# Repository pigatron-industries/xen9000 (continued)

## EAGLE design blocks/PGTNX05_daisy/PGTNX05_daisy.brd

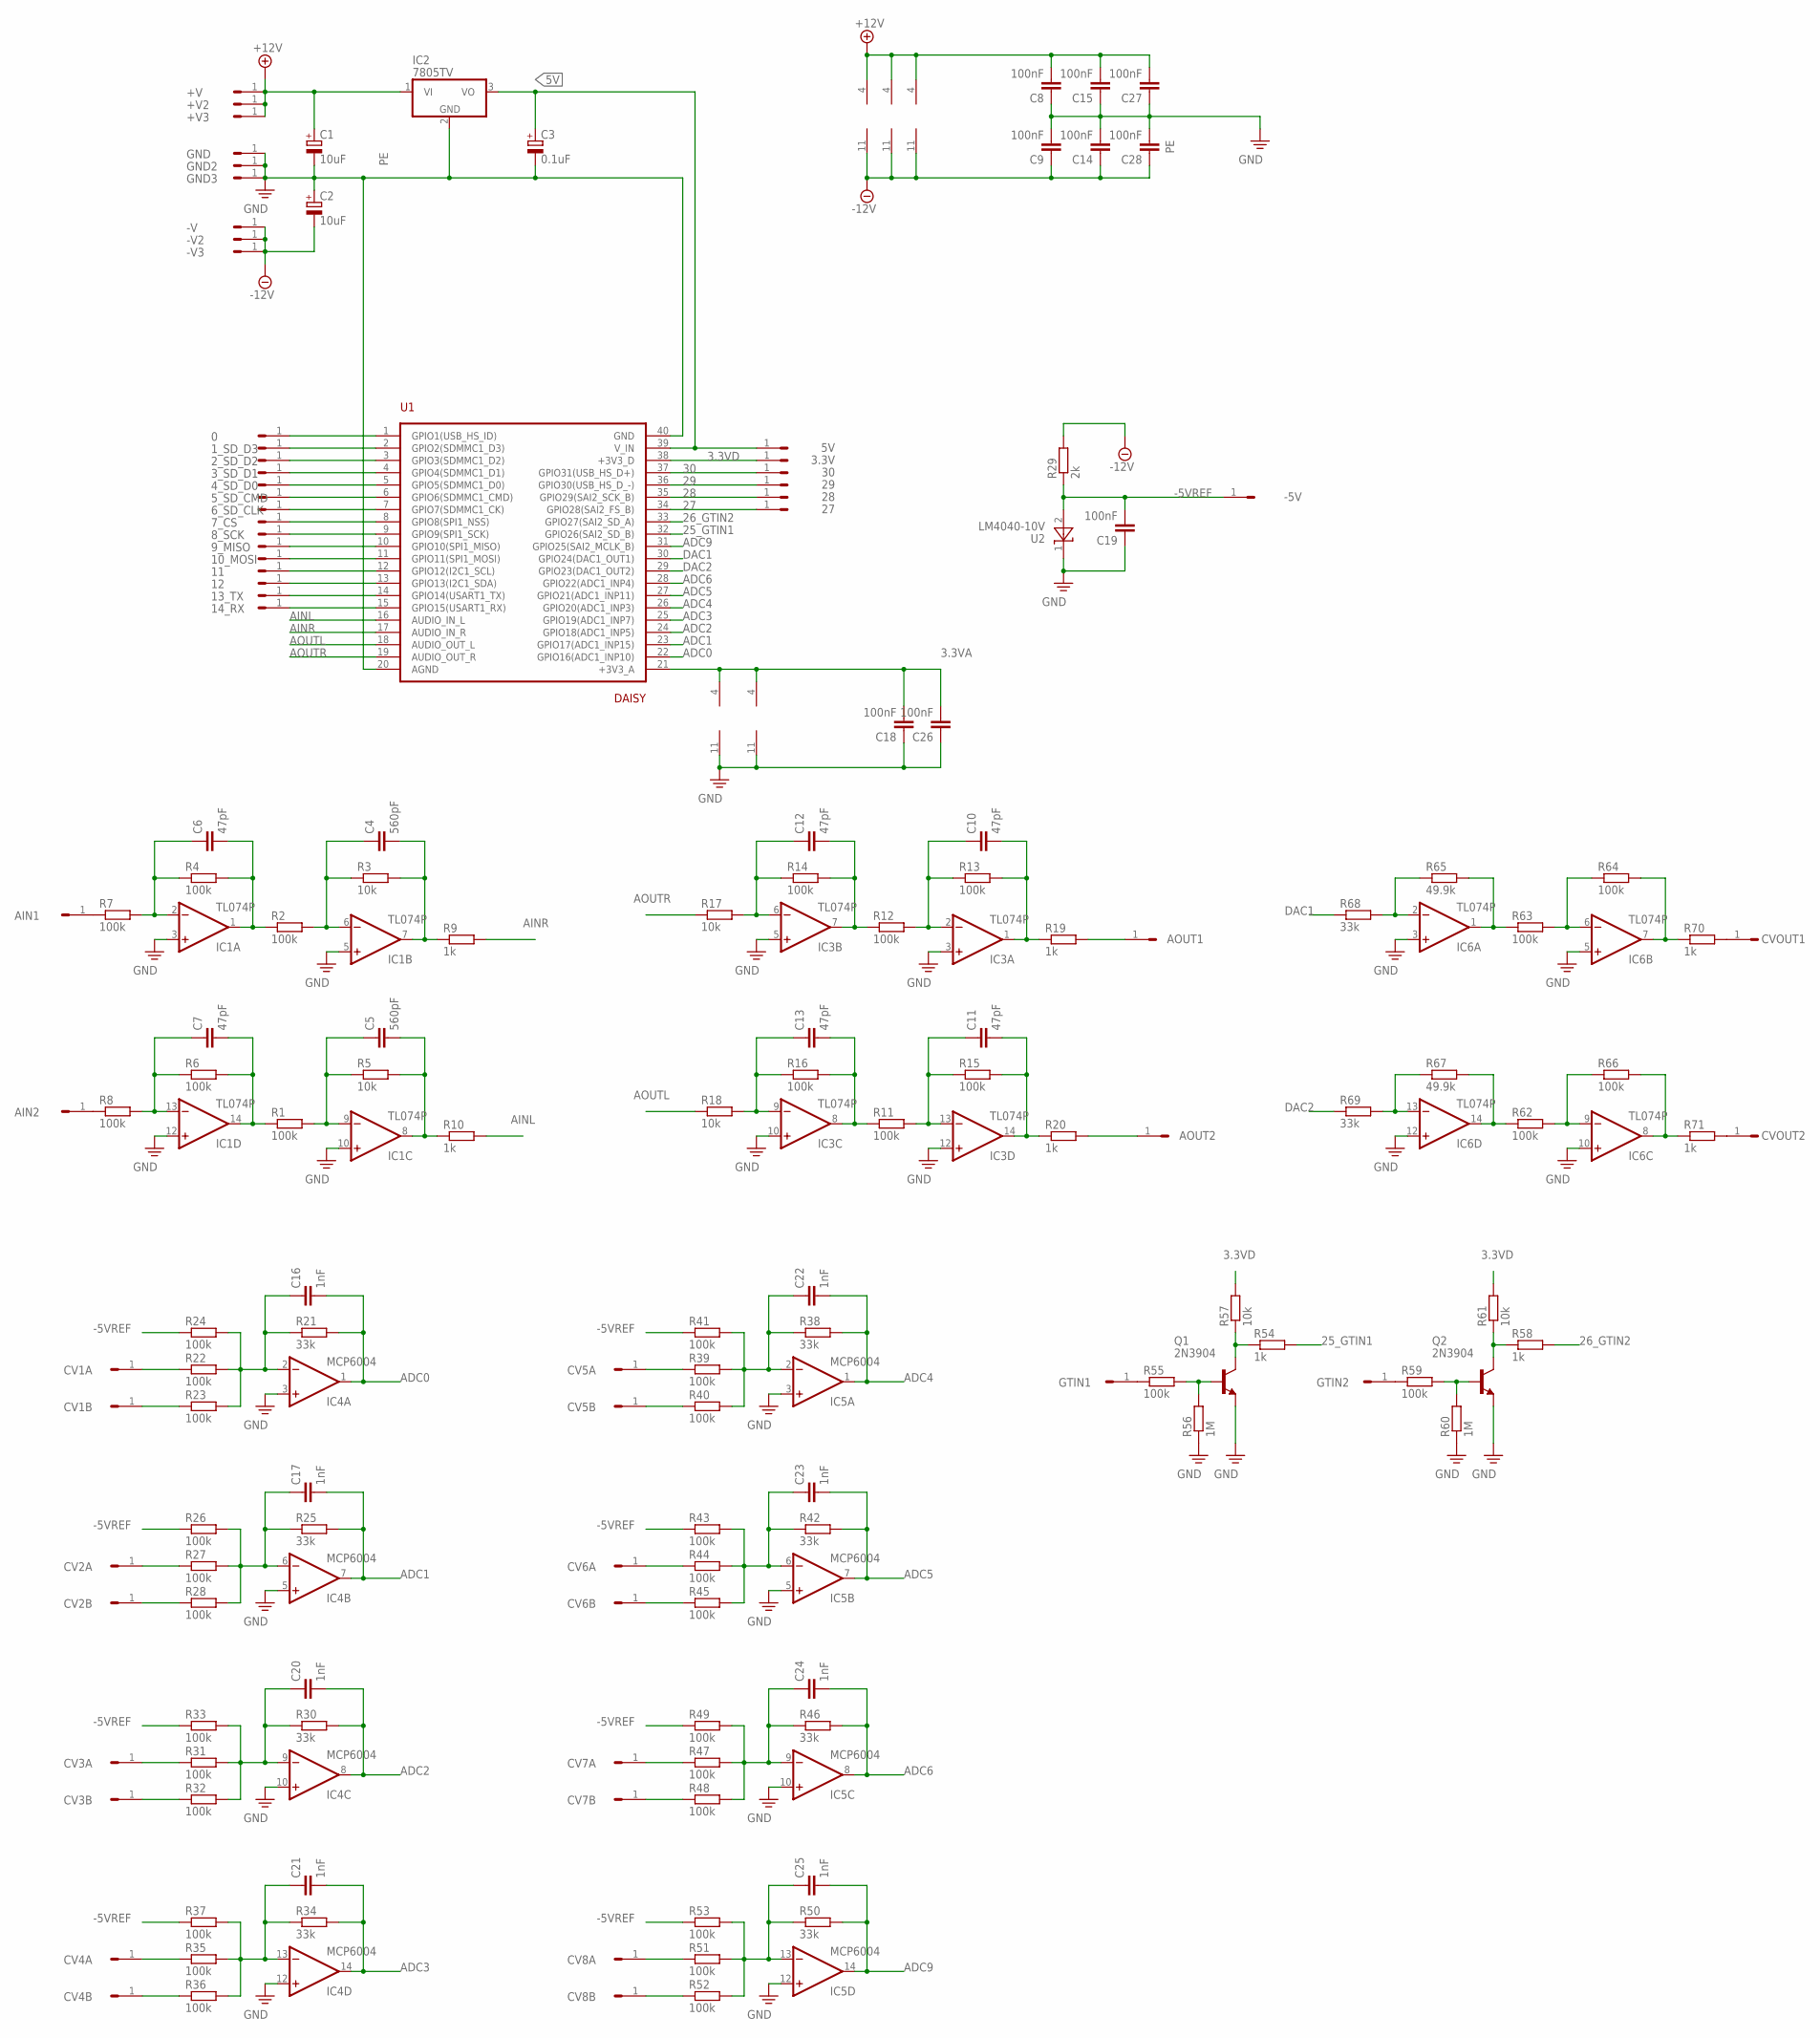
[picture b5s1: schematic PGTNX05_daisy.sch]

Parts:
0, 1_SD_D3, 2_SD_D2, 3.3V, 3_SD_D1, 4_SD_D0, 5V, 5_SD_CMD, 6_SD_CLK, 7_CS, 8_SCK, 9_MISO, 10_MOSI, 11, 12, 13_TX, 14_RX, 27, 28, 29, 30: HEADER/MALE/01
+V, +V2, +V3: HEADER/MALE/01
-5V: HEADER/MALE/01
-V, -V2, -V3: HEADER/MALE/01
AIN1, AIN2: HEADER/MALE/01
AOUT1, AOUT2: HEADER/MALE/01
C1, C2: 10uF; E2,5-6
C3: 0.1uF; E2,5-6
C4, C5: 560pF; CERAMICDISC/5
C6, C7, C10, C11, C12, C13: 47pF; CERAMICDISC/5
C8, C9, C14, C15, C18, C19, C26, C27, C28: 100nF; CERAMICDISC/5
C16, C17, C20, C21, C22, C23, C24, C25: 1nF; CERAMICDISC/5
CV1A, CV1B, CV2A, CV2B, CV3A, CV3B, CV4A, CV4B, CV5A, CV5B, CV6A, CV6B, CV7A, CV7B, CV8A, CV8B: HEADER/MALE/01
CVOUT1, CVOUT2: HEADER/MALE/01
GND, GND2, GND3: HEADER/MALE/01
GTIN1, GTIN2: HEADER/MALE/01
IC1, IC3, IC6: TL074P; DIL14
IC2: 7805TV; TO220V
IC4, IC5: MCP6004; DIL14
Q1, Q2: 2N3904; TO92
R1, R2, R4, R6, R7, R8, R11, R12, R13, R14, R15, R16, R22, R23, R24, R26, R27, R28, R31, R32, R33, R35, R36, R37, R39, R40, R41, R43, R44, R45, R47, R48, R49, R51, R52, R53, R55, R59, R62, R63, R64, R66: 100k; RESISTOR/7.5
R3, R5, R17, R18, R57, R61: 10k; RESISTOR/7.5
R9, R10, R19, R20, R54, R58, R70, R71: 1k; RESISTOR/7.5
R21, R25, R30, R34, R38, R42, R46, R50, R68, R69: 33k; RESISTOR/7.5
R29: 2k; RESISTOR/7.5
R56, R60: 1M; RESISTOR/7.5
R65, R67: 49.9k; RESISTOR/7.5
U1: DAISY; ES_DAISY_SEED
U2: LM4040-10V; SOT-23

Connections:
3.3VA: C18.2, C26.2, IC4.4 (V+), IC5.4 (V+), U1.21 (+3V3_A)
3.3VD: 3.3V.1, R57.2, R61.2, U1.38 (+3V3_D)
5V: 5V.1, C3.+, IC2.3 (VO), U1.39 (V_IN)
25_GTIN1: R54.2, U1.32 (GPIO26(SAI2_SD_B))
26_GTIN2: R58.2, U1.33 (GPIO27(SAI2_SD_A))
27: 27.1, U1.34 (GPIO28(SAI2_FS_B))
28: 28.1, U1.35 (GPIO29(SAI2_SCK_B))
29: 29.1, U1.36 (GPIO30(USB_HS_D_-))
30: 30.1, U1.37 (GPIO31(USB_HS_D+))
+12V: +V.1, +V2.1, +V3.1, C1.+, C8.2, C15.2, C27.2, IC1.4 (V+), IC2.1 (VI), IC3.4 (V+), IC6.4 (V+)
-5VREF: -5V.1, C19.2, R24.1, R26.1, R29.1, R33.1, R37.1, R41.1, R43.1, R49.1, R53.1, U2.2 (A)
-12V: -V.1, -V2.1, -V3.1, C2.-, C9.1, C14.1, C28.1, IC1.11 (V-), IC3.11 (V-), IC6.11 (V-), R29.2
ADC0: C16.2, IC4.1 (OUT), R21.2, U1.22 (GPIO16(ADC1_INP10))
ADC1: C17.2, IC4.7 (OUT), R25.2, U1.23 (GPIO17(ADC1_INP15))
ADC2: C20.2, IC4.8 (OUT), R30.2, U1.24 (GPIO18(ADC1_INP5))
ADC3: C21.2, IC4.14 (OUT), R34.2, U1.25 (GPIO19(ADC1_INP7))
ADC4: C22.2, IC5.1 (OUT), R38.2, U1.26 (GPIO20(ADC1_INP3))
ADC5: C23.2, IC5.7 (OUT), R42.2, U1.27 (GPIO21(ADC1_INP11))
ADC6: C24.2, IC5.8 (OUT), R46.2, U1.28 (GPIO22(ADC1_INP4))
ADC9: C25.2, IC5.14 (OUT), R50.2, U1.31 (GPIO25(SAI2_MCLK_B))
AINL: R10.2, U1.16 (AUDIO_IN_L)
AINR: R9.2, U1.17 (AUDIO_IN_R)
AOUTL: R18.1, U1.18 (AUDIO_OUT_L)
AOUTR: R17.1, U1.19 (AUDIO_OUT_R)
DAC1: R68.1, U1.30 (GPIO24(DAC1_OUT1))
DAC2: R69.1, U1.29 (GPIO23(DAC1_OUT2))
unnamed: CV2A.1, R27.1
unnamed: C7.2, IC1.14 (OUT), R1.1, R6.2
unnamed: C6.2, IC1.1 (OUT), R2.1, R4.2
unnamed: C4.1, IC1.6 (-IN), R2.2, R3.1
unnamed: C5.1, IC1.9 (-IN), R1.2, R5.1
unnamed: AIN1.1, R7.1
unnamed: AIN2.1, R8.1
unnamed: C7.1, IC1.13 (-IN), R6.1, R8.2
unnamed: C5.2, IC1.8 (OUT), R5.2, R10.1
unnamed: C4.2, IC1.7 (OUT), R3.2, R9.1
unnamed: AOUT1.1, R19.2
unnamed: C12.2, IC3.7 (OUT), R12.1, R14.2
unnamed: C6.1, IC1.2 (-IN), R4.1, R7.2
unnamed: C10.1, IC3.2 (-IN), R12.2, R13.1
unnamed: C13.2, IC3.8 (OUT), R11.1, R16.2
unnamed: C11.1, IC3.13 (-IN), R11.2, R15.1
unnamed: C13.1, IC3.9 (-IN), R16.1, R18.2
unnamed: C11.2, IC3.14 (OUT), R15.2, R20.1
unnamed: C10.2, IC3.1 (OUT), R13.2, R19.1
unnamed: C12.1, IC3.6 (-IN), R14.1, R17.2
unnamed: AOUT2.1, R20.2
unnamed: CV1A.1, R22.1
unnamed: 14_RX.1, U1.15 (GPIO15(USART1_RX))
unnamed: C16.1, IC4.2 (-IN), R21.1, R22.2, R23.2, R24.2
unnamed: GTIN2.1, R59.1
unnamed: CV2B.1, R28.1
unnamed: CV1B.1, R23.1
unnamed: 13_TX.1, U1.14 (GPIO14(USART1_TX))
unnamed: C17.1, IC4.6 (-IN), R25.1, R26.2, R27.2, R28.2
unnamed: C21.1, IC4.13 (-IN), R34.1, R35.2, R36.2, R37.2
unnamed: CV4A.1, R35.1
unnamed: CV4B.1, R36.1
unnamed: 10_MOSI.1, U1.11 (GPIO11(SPI1_MOSI))
unnamed: CV3B.1, R32.1
unnamed: CV3A.1, R31.1
unnamed: C20.1, IC4.9 (-IN), R30.1, R31.2, R32.2, R33.2
unnamed: 9_MISO.1, U1.10 (GPIO10(SPI1_MISO))
unnamed: C22.1, IC5.2 (-IN), R38.1, R39.2, R40.2, R41.2
unnamed: 8_SCK.1, U1.9 (GPIO9(SPI1_SCK))
unnamed: CV5B.1, R40.1
unnamed: CV5A.1, R39.1
unnamed: 7_CS.1, U1.8 (GPIO8(SPI1_NSS))
unnamed: C23.1, IC5.6 (-IN), R42.1, R43.2, R44.2, R45.2
unnamed: CV6A.1, R44.1
unnamed: CV6B.1, R45.1
unnamed: C25.1, IC5.13 (-IN), R50.1, R51.2, R52.2, R53.2
unnamed: 6_SD_CLK.1, U1.7 (GPIO7(SDMMC1_CK))
unnamed: CV8A.1, R51.1
unnamed: CV8B.1, R52.1
unnamed: CV7B.1, R48.1
unnamed: CV7A.1, R47.1
unnamed: C24.1, IC5.9 (-IN), R46.1, R47.2, R48.2, R49.2
unnamed: 5_SD_CMD.1, U1.6 (GPIO6(SDMMC1_CMD))
unnamed: GTIN1.1, R55.1
unnamed: Q1.2 (B), R55.2, R56.2
unnamed: Q1.1 (C), R54.1, R57.1
unnamed: Q2.2 (B), R59.2, R60.2
unnamed: Q2.1 (C), R58.1, R61.1
unnamed: 4_SD_D0.1, U1.5 (GPIO5(SDMMC1_D0))
unnamed: 3_SD_D1.1, U1.4 (GPIO4(SDMMC1_D1))
unnamed: 2_SD_D2.1, U1.3 (GPIO3(SDMMC1_D2))
unnamed: 1_SD_D3.1, U1.2 (GPIO2(SDMMC1_D3))
unnamed: 0.1, U1.1 (GPIO1(USB_HS_ID))
unnamed: 11.1, U1.12 (GPIO12(I2C1_SCL))
unnamed: 12.1, U1.13 (GPIO13(I2C1_SDA))
unnamed: IC6.1 (OUT), R63.1, R65.2
unnamed: IC6.6 (-IN), R63.2, R64.1
unnamed: IC6.14 (OUT), R62.1, R67.2
unnamed: IC6.9 (-IN), R62.2, R66.1
unnamed: IC6.13 (-IN), R67.1, R69.2
unnamed: IC6.8 (OUT), R66.2, R71.1
unnamed: IC6.7 (OUT), R64.2, R70.1
unnamed: IC6.2 (-IN), R65.1, R68.2
unnamed: CVOUT1.1, R70.2
unnamed: CVOUT2.1, R71.2
PE: C1.-, C2.+, C3.-, C8.1, C9.2, C14.2, C15.1, C18.1, C19.1, C26.1, C27.1, C28.2, GND.1, GND2.1, GND3.1, IC1.3 (+IN), IC1.5 (+IN), IC1.10 (+IN), IC1.12 (+IN), IC2.2 (GND), IC3.3 (+IN), IC3.5 (+IN), IC3.10 (+IN), IC3.12 (+IN), IC4.3 (+IN), IC4.5 (+IN), IC4.10 (+IN), IC4.11 (V-), IC4.12 (+IN), IC5.3 (+IN), IC5.5 (+IN), IC5.10 (+IN), IC5.11 (V-), IC5.12 (+IN), IC6.3 (+IN), IC6.5 (+IN), IC6.10 (+IN), IC6.12 (+IN), Q1.3 (E), Q2.3 (E), R56.1, R60.1, U1.20 (AGND), U1.40 (GND), U2.1 (C)

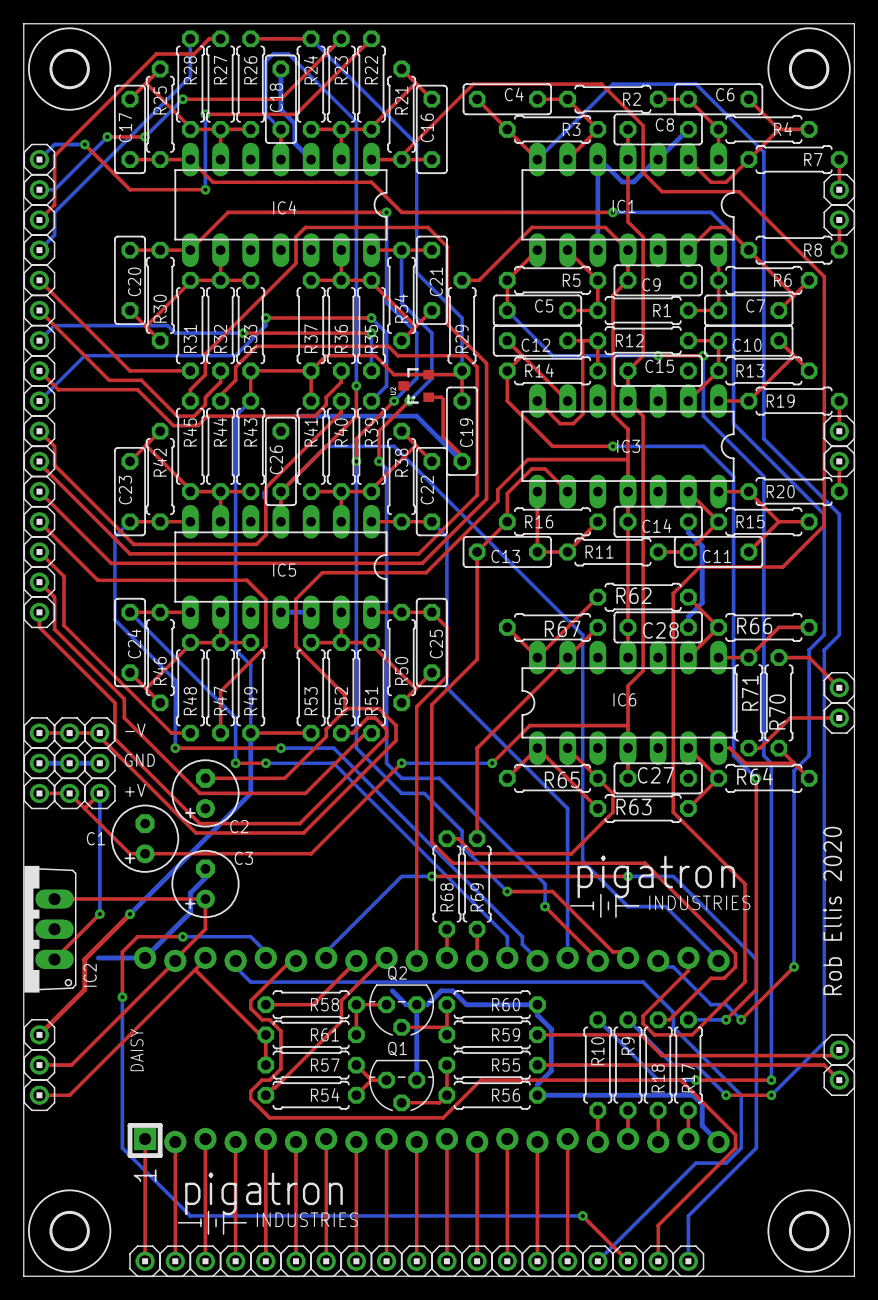
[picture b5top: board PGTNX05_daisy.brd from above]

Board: 2 copper layers, 69.9 x 105.4 mm, 170 parts (0 on the bottom side), 102 nets.

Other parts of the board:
U$1, U$5: PIGATRON-LOGO
U$2, U$3, U$4, U$7: STANDOFF/3.0

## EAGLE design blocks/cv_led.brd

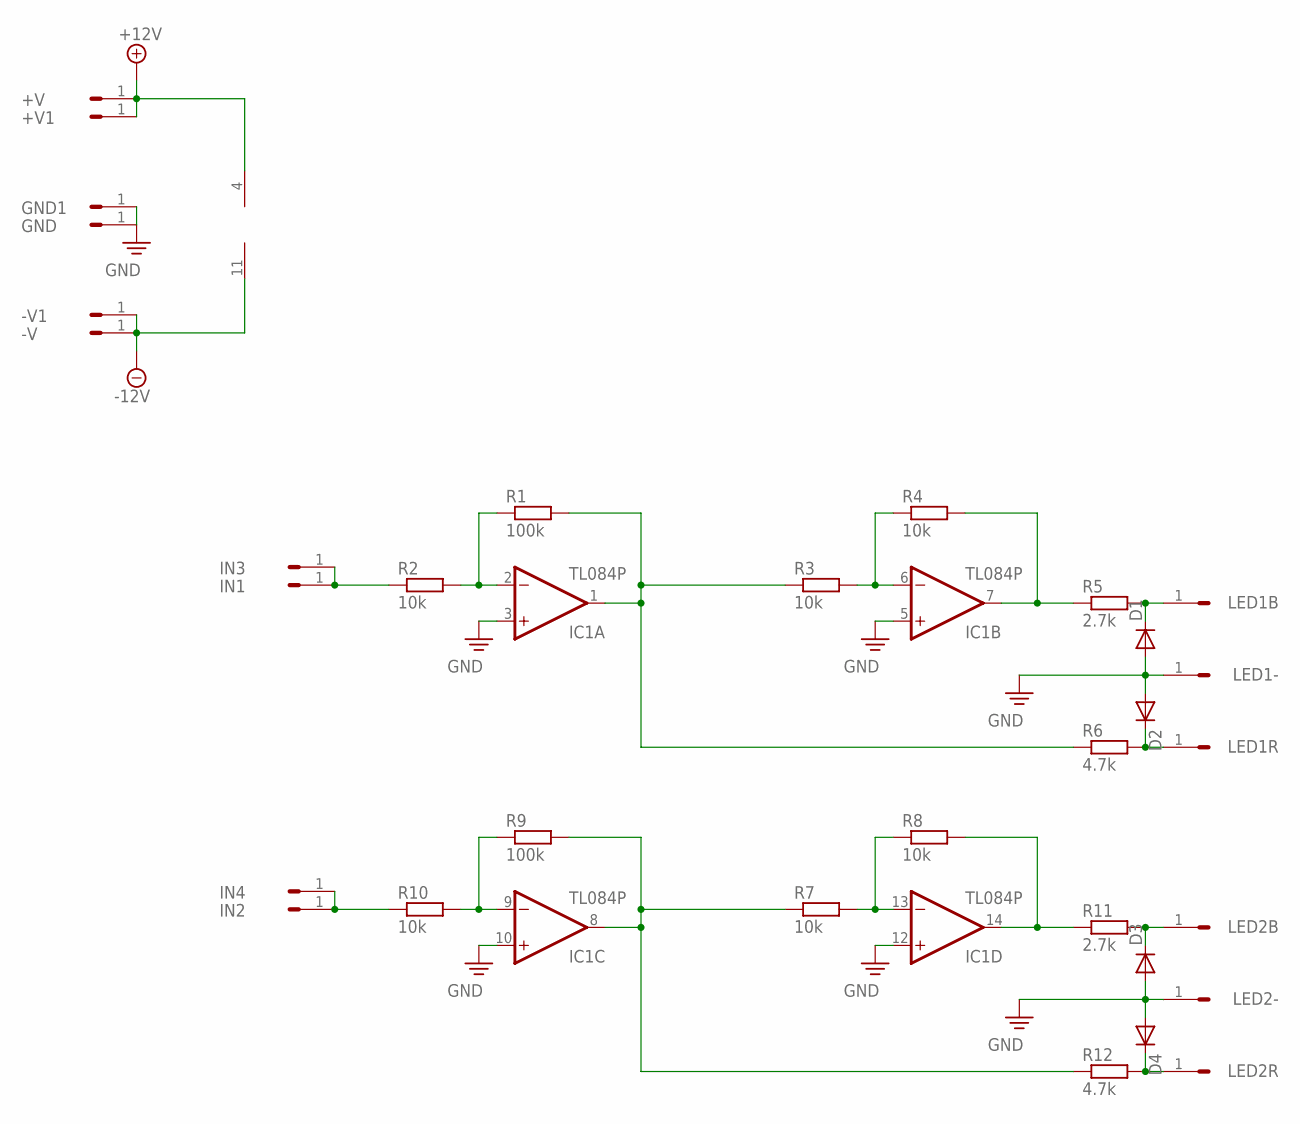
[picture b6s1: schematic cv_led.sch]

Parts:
+V, +V1: HEADER/MALE/01
-V, -V1: HEADER/MALE/01
D1, D2, D3, D4: 1N4148DO35-7; DO35-7
GND, GND1: HEADER/MALE/01
IC1: TL084P; DIL14
IN1, IN2, IN3, IN4: HEADER/MALE/01
LED1-, LED1B, LED1R, LED2-, LED2B, LED2R: HEADER/MALE/01
R1, R9: 100k; RESISTOR/7.5
R2, R3, R4, R7, R8, R10: 10k; RESISTOR/7.5
R5, R11: 2.7k; RESISTOR/7.5
R6, R12: 4.7k; RESISTOR/7.5

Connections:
+12V: +V.1, +V1.1, IC1.4 (V+)
-12V: -V.1, -V1.1, IC1.11 (V-)
GND: D1.A, D2.A, D3.A, D4.A, GND.1, GND1.1, IC1.3 (+IN), IC1.5 (+IN), IC1.10 (+IN), IC1.12 (+IN), LED1-.1, LED2-.1
unnamed: IC1.6 (-IN), R3.2, R4.1
unnamed: IC1.2 (-IN), R1.1, R2.2
unnamed: IC1.1 (OUT), R1.2, R3.1, R6.1
unnamed: IN1.1, IN3.1, R2.1
unnamed: IC1.7 (OUT), R4.2, R5.1
unnamed: D1.C, LED1B.1, R5.2
unnamed: D2.C, LED1R.1, R6.2
unnamed: IC1.13 (-IN), R7.2, R8.1
unnamed: IC1.9 (-IN), R9.1, R10.2
unnamed: IN2.1, IN4.1, R10.1
unnamed: IC1.14 (OUT), R8.2, R11.1
unnamed: IC1.8 (OUT), R7.1, R9.2, R12.1
unnamed: D3.C, LED2B.1, R11.2
unnamed: D4.C, LED2R.1, R12.2

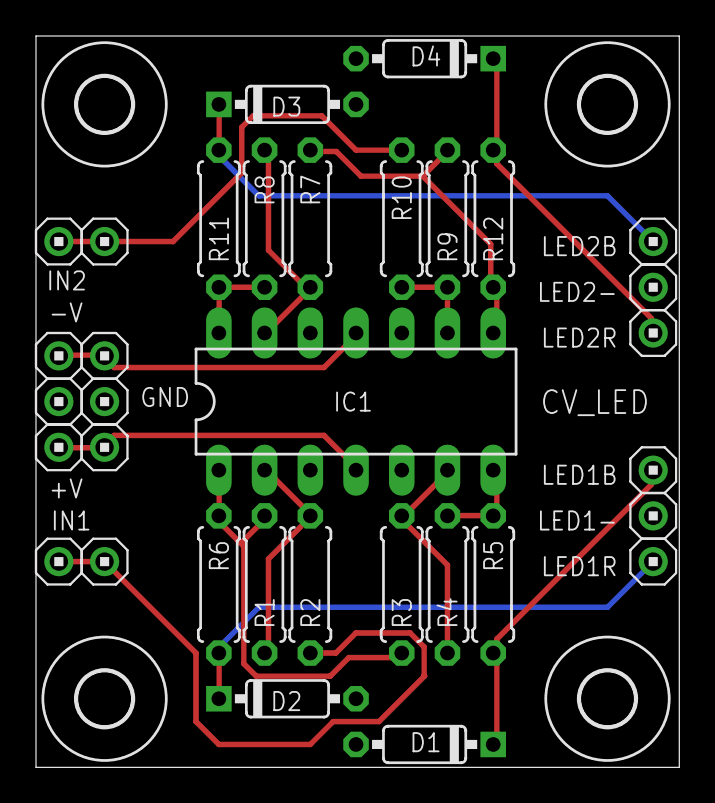
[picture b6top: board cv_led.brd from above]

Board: 2 copper layers, 35.7 x 40.6 mm, 38 parts (1 on the bottom side), 17 nets.

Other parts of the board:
U$1, U$2, U$4, U$5: STANDOFF/3.0
U$3: PIGATRON-LOGO

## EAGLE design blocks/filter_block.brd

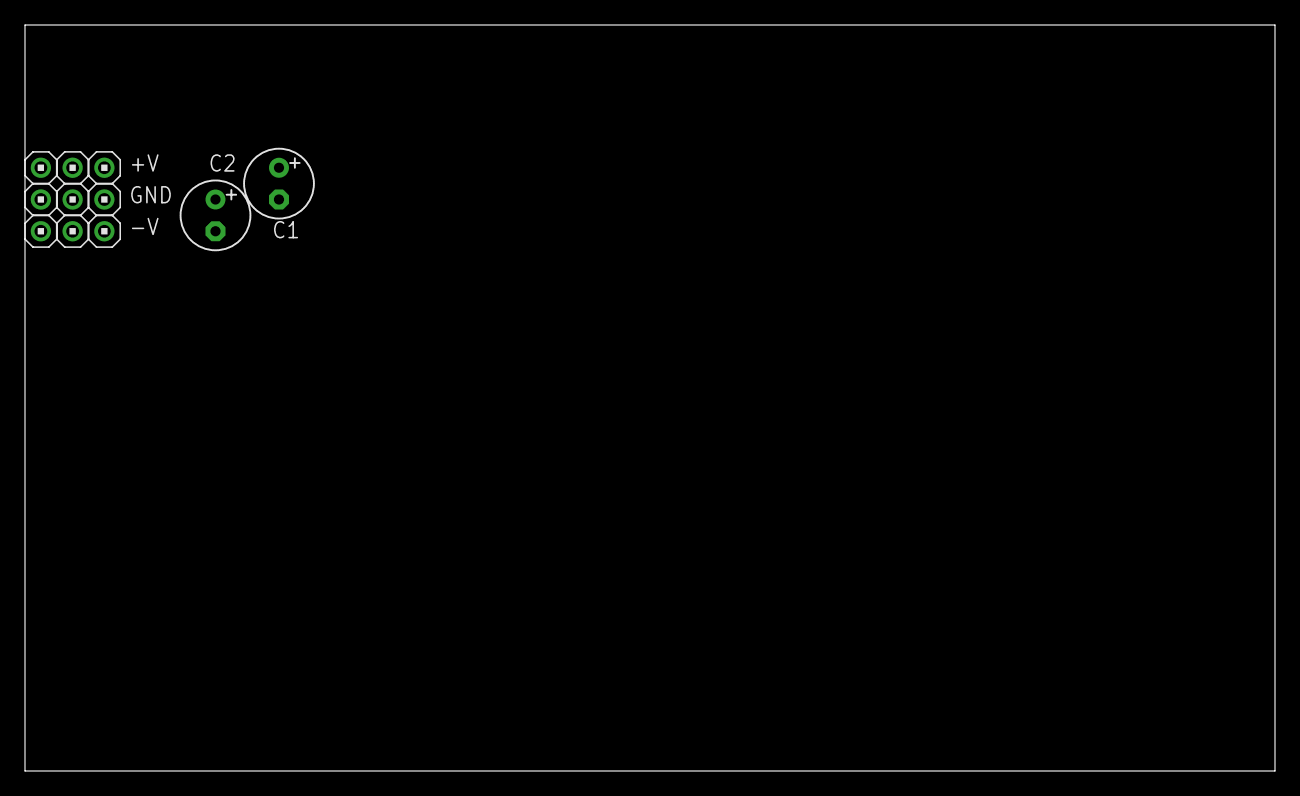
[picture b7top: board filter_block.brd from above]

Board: 2 copper layers, 100.0 x 59.7 mm, 11 parts (0 on the bottom side), 3 nets, no tracks yet.

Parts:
+V, +V2, +V3: HEADER/MALE/01
-V, -V2, -V3: HEADER/MALE/01
C1, C2: 10uF; E2,5-6
GND, GND2, GND3: HEADER/MALE/01

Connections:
+12V: +V.1, +V2.1, +V3.1, C1.+
-12V: -V.1, -V2.1, -V3.1, C2.-
GND: C1.-, C2.+, GND.1, GND2.1, GND3.1
